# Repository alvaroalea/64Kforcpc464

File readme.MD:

# 64Kb RAM Upgrade for CPC 464

# THIS SCHEMATIC DO NOT WORK
## THIS DO NOT WORK "YET" NOT FOR USE, THIS IS ONLY A MOCKUP, WORK IN PROGRESS

(C) 2018 Alvaro Alea Fernandez.

This work is licensed under a Creative Commons Attribution-NonCommercial-ShareAlike 4.0 International License.

http://creativecommons.org/licenses/by-nc-sa/4.0/

Some ideas I was catching from internet to make a clone of the dk'tronic 64Kb RAM expansion.
With a DD-1 interface this allow to convert a CPC464 into a CPC6128

More info (in spanish) here:
http://www.va-de-retro.com/foros/viewtopic.php?f=63&t=7204
https://docs.google.com/document/d/1A2S5vsXNrJ32xeh1cSbQ3WHVme9vBhbhzmRaSeRBW9Q/edit?usp=sharing

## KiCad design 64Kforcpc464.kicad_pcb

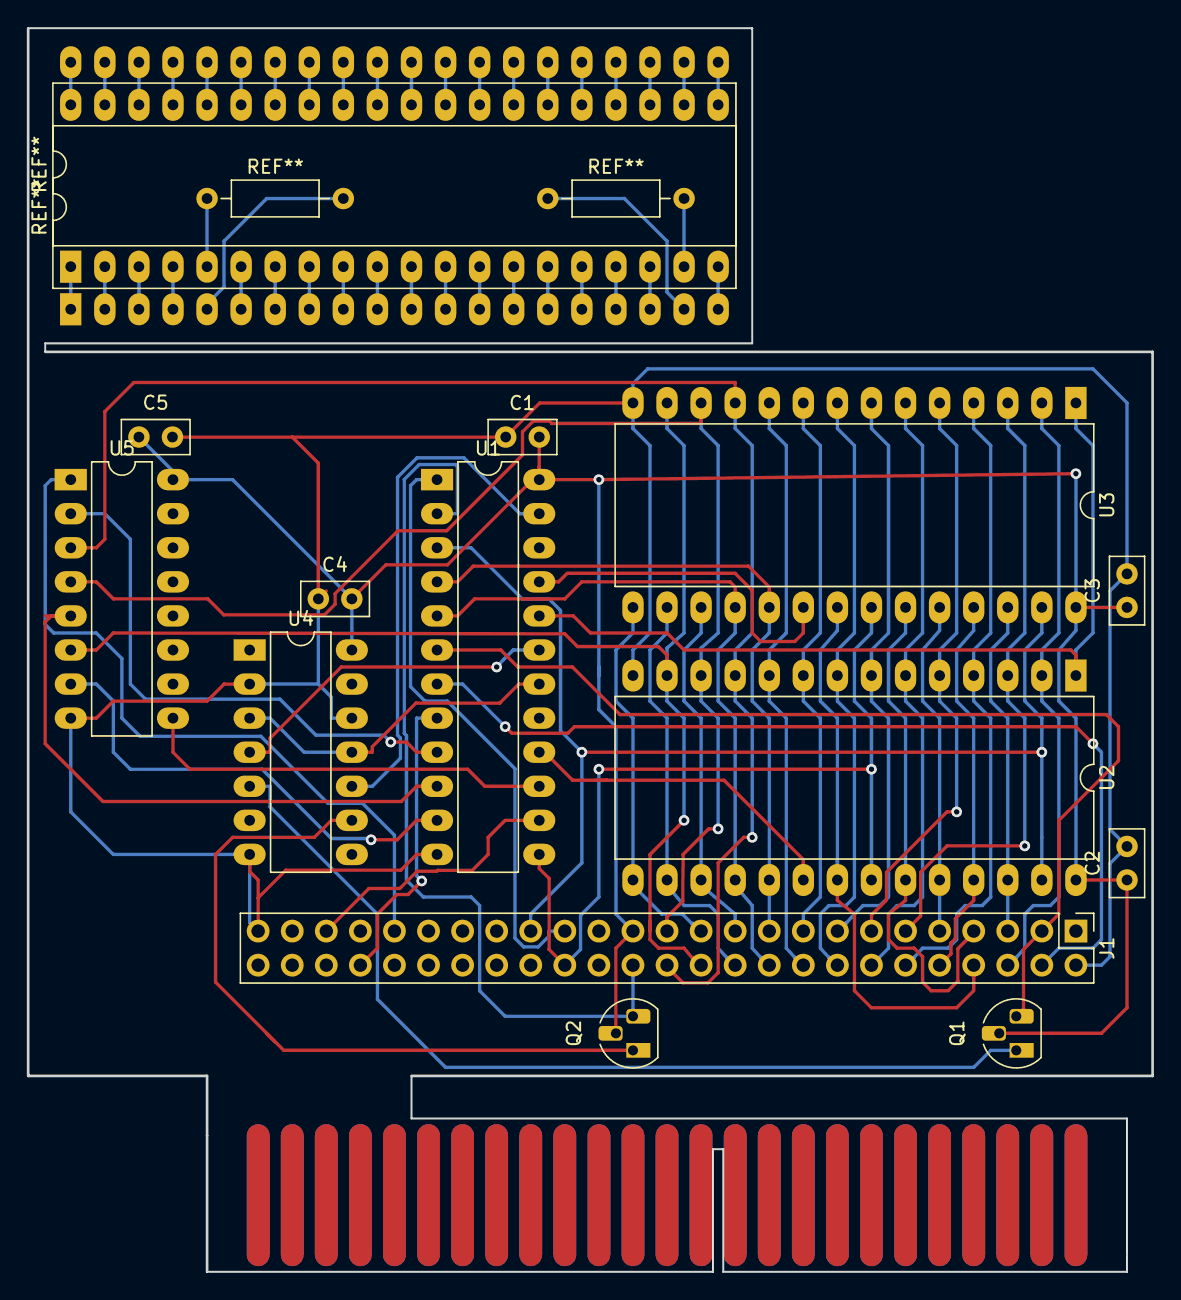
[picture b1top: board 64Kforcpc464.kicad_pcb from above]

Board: 2 copper layers, 83.8 x 92.7 mm, 13 parts (0 on the bottom side), 45 nets.

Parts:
C1, C2, C3, C4, C5: 100n; C_Disc_D5.0mm_W2.5mm_P2.50mm
J1: Conn_02x25_Odd_Even; PinHeader_2x25_P2.54mm_Vertical
Q1, Q2: Q_NPN_BCE; TO-92_HandSolder
U1: GAL22V10; DIP-24_W7.62mm_LongPads
U2, U3: 62256; DIP-28_W15.24mm_LongPads
U4: 74LS74; DIP-14_W7.62mm_LongPads
U5: 74LS174; DIP-16_W7.62mm_LongPads

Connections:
+5V: C1.1, C2.1, C3.1, C4.1, C5.1, J1.27, Q1.2, Q2.2, U1.24, U2.28, U3.28, U4.14, U5.16
/A0: J1.18, U2.10, U3.10
/A1: J1.17, U2.9, U3.9
/A2: J1.16, U2.8, U3.8
/A3: J1.15, U2.7, U3.7
/A4: J1.14, U2.6, U3.6
/A5: J1.13, U2.5, U3.5
/A6: J1.12, U2.4, U3.4
/A7: J1.11, U2.3, U3.3
/A8: J1.10, U2.25, U3.25
/A9: J1.9, U2.24, U3.24
/A10: J1.8, U2.21, U3.21
/A11: J1.7, U2.23, U3.23
/A12: J1.6, U2.2, U3.2
/A13: J1.5, U2.26, U3.26
/A14: J1.4, U1.7
/D0: J1.26, U2.11, U3.11, U5.3
/D1: J1.25, U2.12, U3.12, U5.4
/D2: J1.24, U2.13, U3.13, U5.6
/D3: J1.23, U2.15, U3.15
/D4: J1.22, U2.16, U3.16
/D5: J1.21, U2.17, U3.17
/D6: J1.20, U1.5, U2.18, U3.18
/D7: J1.19, U1.4, U2.19, U3.19
/IOREQ: J1.31, U1.1
/RAM_RD: J1.44, U1.8
/RD: J1.32, U1.13, U2.22, U3.22
/RESET: J1.41, U5.1
/WR: J1.33, U1.3, U2.27, U3.27
A15: J1.3, Q1.3, U1.6
END_FORCE: U1.18, U4.3, U4.11
FORCE_A15: U1.19, U4.4
FORCE_MREQ: U1.23, U4.10
GND: C1.2, C2.2, C3.2, C4.2, C5.2, J1.2, J1.49, U1.12, U2.14, U3.14, U4.2, U4.7, U4.12, U5.8
MREQ: J1.28, Q2.3, U1.2
unnamed: Q1.1, U4.5
unnamed: Q2.1, U4.9
unnamed: U1.9, U5.2
unnamed: U1.10, U5.5
unnamed: U1.11, U5.7
unnamed: U1.15, U5.9
RAM1_CE: U1.16, U2.20
RAM2_CE: U1.21, U3.20
RAM_A14: U1.20, U2.1, U3.1
RAM_DIS: J1.45, U1.14

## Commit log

2018-09-01 inicial
2018-09-01 initial
2018-09-01 try to compile #1
2022-02-13 update (C)

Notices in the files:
readme.MD:
CC BY-NC-SA 4.0
